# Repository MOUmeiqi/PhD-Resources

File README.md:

# PhD-Resources
Source code repository for PhD on OCDM-aEITS

*** README ***

This repository (repo) contains the source code and some experimental results acquired during research of the thesis titled "Absolute Electrical Impedance Tomography and Spectroscopy - An Orthogonal Chirp Division Multiplexed (OCDM) Approach"
This thesis was authored by: Ezra Luke America and presented to the University of Cape Town for fulfilment of a Doctorate of Philosophy in Electrical Engineering.

The repo separated into four streams:
1) Source Codes
2) Misc. Experimental Results
3) Schematics
4) Misc. Images

*** Codes ***
The source codes components of the repo holds the source files that were used for the Arduino, MATLAB, uDAQ, and FPGA.
The code for the Arduino was used to control the system wide multiplexing.
The code for MATLAB was used to control the entire system and reconstruct images.
The code for the uDAQ_test_scripts were used to control a data acquisition card when initial tests were performed.
The code for the VHDL_CODE were used to control the ADC/DAC data acquisition board and FPGA.

*** Misc. Experimental Results ***
This folder contains 8 internal folders that hold a measurement frame for eight different positions of an anomaly.
To test this data, import the data to the MATLAB image_reconstruction code in the MATLAB folder.

*** Schematics ***
The schematics folder contains some system design schematics.

*** Misc. Images ***
This folder contains some reconstructed images using higher element FEM models.

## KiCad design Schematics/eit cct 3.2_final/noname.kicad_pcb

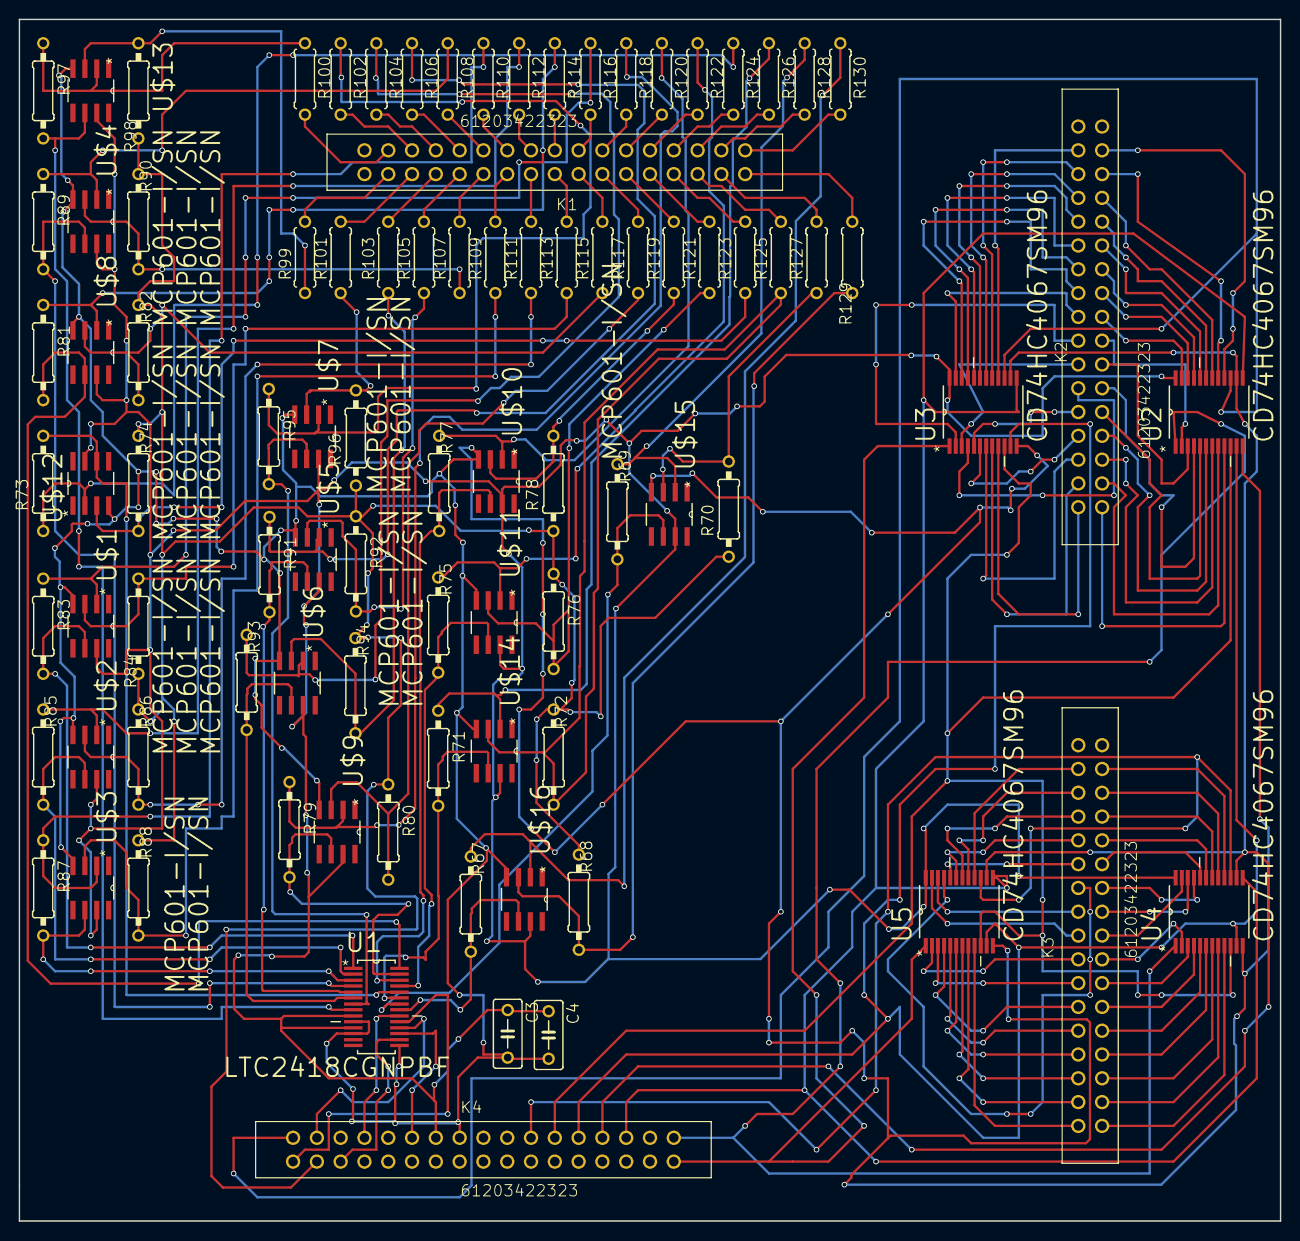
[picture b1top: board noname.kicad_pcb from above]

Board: 2 copper layers, 134.6 x 128.3 mm, 91 parts (0 on the bottom side), 160 nets.

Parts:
C3, C4: C050-030X075
K1, K2, K3, K4: 61203422323
R67, R68, R69, R70, R71, R72, R73, R74, R75, R76, R77, R78, R79, R80, R81, R82, R83, R84, R85, R86, R87, R88, R89, R90, R91, R92, R93, R94, R95, R96, R97, R98: 0207%2f10
R99, R100, R101, R102, R103, R104, R105, R106, R107, R108, R109, R110, R111, R112, R113, R114, R115, R116, R117, R118, R119, R120, R121, R122, R123, R124, R125, R126, R127, R128, R129, R130: 0207%2f7
U1: LTC2418CGNPBF; SOP63P600X175-28N
U2, U3, U4, U5: CD74HC4067SM96; SOP65P780X200-24N
U$1, U$2, U$3, U$4, U$5, U$6, U$7, U$8, U$9, U$10, U$11, U$12, U$13, U$14, U$15, U$16: MCP601-I/SN; SOIC127P600X175-8N

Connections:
GND: C3.2, C4.2, K4.16, U1.10, U1.12, U1.15, U2.12, U3.12, U4.12, U5.12, U$1.4, U$2.4, U$3.4, U$4.4, U$5.4, U$6.4, U$7.4, U$8.4, U$9.4, U$10.4, U$11.4, U$12.4, U$13.4, U$14.4, U$15.4, U$16.4
unnamed: R67.2, U1.21, U$16.6
unnamed: R71.2, U1.23, U$14.6
unnamed: R73.2, U1.24, U$12.6
unnamed: R75.2, U1.25, U$11.6
unnamed: R77.2, U1.26, U$10.6
unnamed: R79.2, U1.27, U$9.6
unnamed: R81.2, U1.28, U$8.6
unnamed: R83.2, U1.1, U$1.6
unnamed: R85.2, U1.2, U$2.6
unnamed: R87.2, U1.3, U$3.6
unnamed: R89.2, U1.4, U$4.6
unnamed: R91.2, U1.5, U$5.6
unnamed: R93.2, U1.6, U$6.6
unnamed: R95.2, U1.7, U$7.6
unnamed: R97.2, U1.8, U$13.6
unnamed: K4.3, R68.1, R70.1, R72.1, R74.1, R76.1, R78.1, R80.1, R82.1, R84.1, R86.1, R88.1, R90.1, R92.1, R94.1, R96.1, R98.1
unnamed: R94.2, R103.1, U$6.3
unnamed: R92.2, R105.1, U$5.3
unnamed: R67.1, R130.1, U$16.2
unnamed: R90.2, R107.1, U$4.3
unnamed: R68.2, R129.1, U$16.3
unnamed: R88.2, R109.1, U$3.3
unnamed: R69.1, R128.1, U$15.2
unnamed: R70.2, R127.1, U$15.3
unnamed: R86.2, R111.1, U$2.3
unnamed: R71.1, R126.1, U$14.2
unnamed: R84.2, R113.1, U$1.3
unnamed: R82.2, R115.1, U$8.3
unnamed: R73.1, R124.1, U$12.2
unnamed: R80.2, R117.1, U$9.3
unnamed: R75.1, R122.1, U$11.2
unnamed: R78.2, R119.1, U$10.3
unnamed: R77.1, R120.1, U$10.2
unnamed: R76.2, R121.1, U$11.3
unnamed: R79.1, R118.1, U$9.2
unnamed: R74.2, R123.1, U$12.3
unnamed: R81.1, R116.1, U$8.2
unnamed: R72.2, R125.1, U$14.3
unnamed: R83.1, R114.1, U$1.2
unnamed: K1.2, R129.2
unnamed: R85.1, R112.1, U$2.2
unnamed: K1.1, R130.2
unnamed: R87.1, R110.1, U$3.2
unnamed: K1.4, R127.2
unnamed: R89.1, R108.1, U$4.2
unnamed: K1.3, R128.2
unnamed: R91.1, R106.1, U$5.2
unnamed: K1.6, R125.2
unnamed: R93.1, R104.1, U$6.2
unnamed: K1.5, R126.2
unnamed: R95.1, R102.1, U$7.2
unnamed: K1.8, R123.2
unnamed: R97.1, R100.1, U$13.2
unnamed: K1.7, R124.2
unnamed: R98.2, R99.1, U$13.3
unnamed: K1.10, R121.2
unnamed: R96.2, R101.1, U$7.3
unnamed: K1.9, R122.2
unnamed: K1.12, R119.2
unnamed: K1.11, R120.2
unnamed: K1.14, R117.2
unnamed: K1.19, R112.2
unnamed: K1.16, R115.2
unnamed: K1.15, R116.2
unnamed: K1.18, R113.2
unnamed: K1.17, R114.2
unnamed: K1.20, R111.2
unnamed: K4.1, U1.19
unnamed: K1.22, R109.2
unnamed: K1.21, R110.2
unnamed: K1.24, R107.2
unnamed: K1.26, R105.2
unnamed: K1.25, R106.2
unnamed: K1.23, R108.2
unnamed: K1.28, R103.2
unnamed: K1.27, R104.2
unnamed: K1.30, R101.2
unnamed: K1.29, R102.2
unnamed: K1.32, R99.2
unnamed: K1.31, R100.2
unnamed: K2.1, U2.9
unnamed: K2.2, U3.9
unnamed: K2.3, U2.8
unnamed: K2.4, U3.8
unnamed: K2.5, U2.7
unnamed: K2.6, U3.7
unnamed: K2.7, U2.6
unnamed: K2.8, U3.6
unnamed: K2.9, U2.5
unnamed: K2.10, U3.5
unnamed: K2.12, U3.4
unnamed: K2.14, U3.3
unnamed: K2.16, U3.2
unnamed: K2.18, U3.23
unnamed: K2.20, U3.22
unnamed: K2.22, U3.21
unnamed: K2.24, U3.20
unnamed: K2.26, U3.19
unnamed: K2.28, U3.18
unnamed: K2.30, U3.17
unnamed: K2.32, U3.16
unnamed: K2.11, U2.4
unnamed: K2.13, U2.3
unnamed: K2.15, U2.2
unnamed: K2.17, U2.23
unnamed: K2.19, U2.22
unnamed: K2.21, U2.21
unnamed: K2.23, U2.20
unnamed: K2.25, U2.19
unnamed: K2.27, U2.18
unnamed: K2.29, U2.17
unnamed: K2.31, U2.16
unnamed: K3.1, U4.9
unnamed: K3.3, U4.8
unnamed: K3.5, U4.7
unnamed: K3.7, U4.6
unnamed: K3.9, U4.5
unnamed: K3.11, U4.4
unnamed: K3.13, U4.3
unnamed: K3.15, U4.2
unnamed: K3.17, U4.23
unnamed: K3.19, U4.22
unnamed: K3.21, U4.21
unnamed: K3.23, U4.20
unnamed: K3.25, U4.19
unnamed: K3.27, U4.18
unnamed: K3.29, U4.17
unnamed: K3.31, U4.16
unnamed: K3.2, U5.9
unnamed: K3.4, U5.8
unnamed: K3.6, U5.7
unnamed: K3.8, U5.6
unnamed: K3.10, U5.5
unnamed: K3.12, U5.4
unnamed: K3.14, U5.3
unnamed: K3.16, U5.2
unnamed: K3.18, U5.23
unnamed: K3.20, U5.22
unnamed: K3.22, U5.21
unnamed: K3.24, U5.20
unnamed: K3.26, U5.19
unnamed: K3.28, U5.18
unnamed: K3.30, U5.17
unnamed: K3.32, U5.16
unnamed: K4.5, U1.16
unnamed: K4.4, U1.18
unnamed: K4.8, U1.20
unnamed: K4.12, U1.17
unnamed: K4.28, U2.14, U3.14, U4.14, U5.14
unnamed: K4.2, U2.15, U3.15
unnamed: K1.13, R118.2
unnamed: K4.22, U4.15, U5.15
unnamed: K4.26, U2.11, U3.11, U4.11, U5.11
unnamed: K4.30, U2.13, U3.13, U4.13, U5.13
unnamed: R69.2, U1.22, U$15.6
unnamed: K4.34, U2.1, U4.1
unnamed: K4.33, U3.1, U5.1
unnamed: K4.24, U2.10, U3.10, U4.10, U5.10
VCC: C3.1, C4.1, K4.14, U1.9, U1.11, U2.24, U3.24, U4.24, U5.24, U$1.7, U$2.7, U$3.7, U$4.7, U$5.7, U$6.7, U$7.7, U$8.7, U$9.7, U$10.7, U$11.7, U$12.7, U$13.7, U$14.7, U$15.7, U$16.7
